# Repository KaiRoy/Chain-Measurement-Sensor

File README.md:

# Chain-Measurement-Sensor
The focus of this project was to create a Sensor that measures the wear of a chain for our Senior design course. The project partner for this project was the Hyster-Yale Group.

<!-- Insert Image Here -->

<!-- LINK SUMMARY VIDEO SOMEWHERE IN THE README!! -->

## Table of Contents

- [Description](#description)
- [Design](#design)
- [Current State](#current-state-of-the-project)
- [Post Project Notes](#post-project-notes)
- [Installation](#installation) <!-- Should I have Installation and Usage above or below the Design, Current State, Changes, etc? -->
- [Usage](#usage)
- [Credits](#credits)
- [License](#license)

## Description

The goal of this project is to create a chain elongation monitor for the Hyster-Yale Group that will automatically detect a worn lift chain and notify an operator to replace said chain. Chains, especially lifting chains, need to be frequently inspected to ensure they meet specifications. A 3% increase in a chain’s length can reduce its lifting capacity by 15%. This can become a dangerous hazard if out-of-spec chains are not caught. 

Currently, this inspection is either done by hand or by expensive third party devices, thus the creation of a cheap electronic alternative is very desirable. We plan to use three pairs of IR LEDs and IR receivers that will act as our sensors. These pairs will be situated in such a way that the IR “beam” will break when a chain link passes the sensor and reconnect in the gap between chain links. One pair will be used to measure the speed, while the other two will measure the “stretch” of the chain by recording the time difference between activations and calculating a length measurement.

In addition to the sensors, the device will consist of a power circuit to convert a Forklift’s 24V power into 5Vs, a CAN communication circuit, and a microcontroller to calculate the elongation based on the sensors and send those measurements via the CAN Circuit to the Hyster Vehicle. We chose an ATTiny814 for our microcontroller as it is a relatively small and cheap microcontroller and is capable of performing necessary functions, such as basic calculations and time measurement. 

Our project partner has specified that the device needs to meet four requirements:
 - The device needs to measure chain “stretch” (wear) within ±5% of the actual measurement.
 - The device, specifically the electronics, need to cost less than $15 or less at a production quantity of 15,000/yr
 - The device need to be robust enough to survive abrasive (high chain wear) applications
 - The device needs to communicate using the CAN communication protocol

At the end of our project, we were able to meet 3 of the 4 project partner requirements with the accuracy requirement being the one that was not met. This is mostly due to not having enough time to finish experimenting and debugging the code. With better time management and planning, we would have been able to finish the development of our code and could have met the final requirement.

## Designs

For the design portion of this project, the system's design was split into eight blocks with each person handling the design for two blocks. Adam handled the design of the Power Filter and the Power Regulator Blocks. Tianhao designed the Microcontroller and CAN Communication Circuits. The sensor and PCB blocks were handled by Kai. The code and the enclosure blocks were designed by Corbin. 

<!-- Power Blocks -->
The power converter block is based on an application schematic from the MC34063A-E datasheet to be used as a step-down converter. This block accomplishes the goal of reducing voltage and increasing current from 25V to 5V and current up to 500mA. The goal is to make the voltage and current levels safe for our microcontroller, CAN controller, and sensors to be used properly without overheating. The block contains the MC34063A/E chip itself, IN5819 Zener diode, three resistors (two are external to control the voltage output), three capacitors, and one inductor.

The power filter block is based on the LC filter schematic from [Digikey’s online LC filter calculator](https://www.digikey.com/en/resources/conversion-calculators/conversion-calculator-low-pass-and-high-pass-filter) to be used as a first order LC filter. This block accomplishes the goal of reducing frequency down to a fixed value of about less than 16kHz. This is to ensure that our high noise level of frequency is reduced so that our microcontroller and sensors can operate effectively. The block contains one inductor and one capacitor.

<!-- CAN Controller-->
The can block is built with one of the most practical stand-alone CAN controllers, MCP 2515 as the core. This module achieves the goal of communicating with Hyster Forklift’s electronics via 5 V digital serial signal. After achieving this goal, we can connect our device to the forklift with only two wires, so that the forklift can receive any information accurately. In this block, in addition to MCP 2515, we will also use TJA 1051 as the transceiver of the block to transmit or receive information transmitted through the CAN bus, an 8M Hz crystal oscillator as a bit rate regulator, an LED as an indicator, and some resistors and capacitors to stabilize the voltage and current of the part. In addition, we will also add two terminal block connectors to allow the output of the signal to adapt to more kinds of wires.

<!-- Micrcontroller -->
The Microcontroller block to be used in this project is the ATtiny 814. The module will be responsible for collecting and analyzing signals from the sensor, as well as controlling the operation of the signal transmitter. With the ATtiny 814, the project aims to achieve certain targets, such as measuring chain "stretch" within +/- 5% of the actual measurement, costing less than $10 at a production quantity of 15,000/yr, and outputting an analog (5V) or digital signal (CAN or other serial protocol signal).

<!-- Sensors -->
The Sensor block is implemented using three IR Breakbeam sensors. This document provides an overview of the overall block function including interface properties and a schematic, verification for the design in the form of a step-by-step testing process, and support for the validity of the design in the form of outside research and numerical justification addressing individual properties.

One sensor is placed in the ‘middle’ middle of the device and will be for measuring the speed of the Chain, while two sensors will be placed on the outer edges of the device and will be used for measuring/detecting the elongation of the chain.

The measurement of speed can be done by measuring the time difference between sensor activation as a chain link crosses the two central sensors and calculating the speed with that delta and the chain link length. For the elongation measurement/monitoring, the outer two sensors are placed with a specific distance between them, X amount of chain links. If positioned correctly, the two sensors will activate simultaneously with a chain that is not elongated and activates with some time delta with a chain that is elongated. This time delta coupled with the calculated speed can provide an estimate for the elongation measurement.

<!-- PCB -->
The Final PCB contains most of the circuits for all of the electronics blocks of the system. These circuits include the Power Filter, Power Converter, Microcontroller, and CAN Controller Blocks. This means that all of the outward-facing interfaces for these blocks, such as the sensor, power, and CAN connectors, are the interfaces for this block. 

<!-- Enclosure -->
The enclosure for this project will be a durable Pelican Case, created and distributed by the Pelican company. This ensures that our enclosure will be consistent, professionally made, and strong enough to protect our fragile components from the dangerous environment they will have to be in. Additionally, a piece of acrylic will be laser cut to allow for the mounting of the PCB and the guiding of wires through the walls of the enclosure, which will have holes cut into it.

## Current State of the Project

By the end of the project, we had a mostly working system. 

## Post Project Notes

## Installation

What EDA libraries and files are needed for this project?
- Various Component Libraries

<!--
## Usage

Provide instructions and examples for use. Include screenshots as needed.

To add a screenshot, create an `assets/images` folder in your repository and upload your screenshot to it. Then, using the relative filepath, add it to your README using the following syntax:

    ```md
    
    ```

## Features

If your project has a lot of features, list them here.

## Tests

-->

## Credits

List your collaborators, if any, with links to their GitHub profiles.
- Kai Roy
- 

If you used any third-party assets that require attribution, list the creators with links to their primary web presence in this section.
-

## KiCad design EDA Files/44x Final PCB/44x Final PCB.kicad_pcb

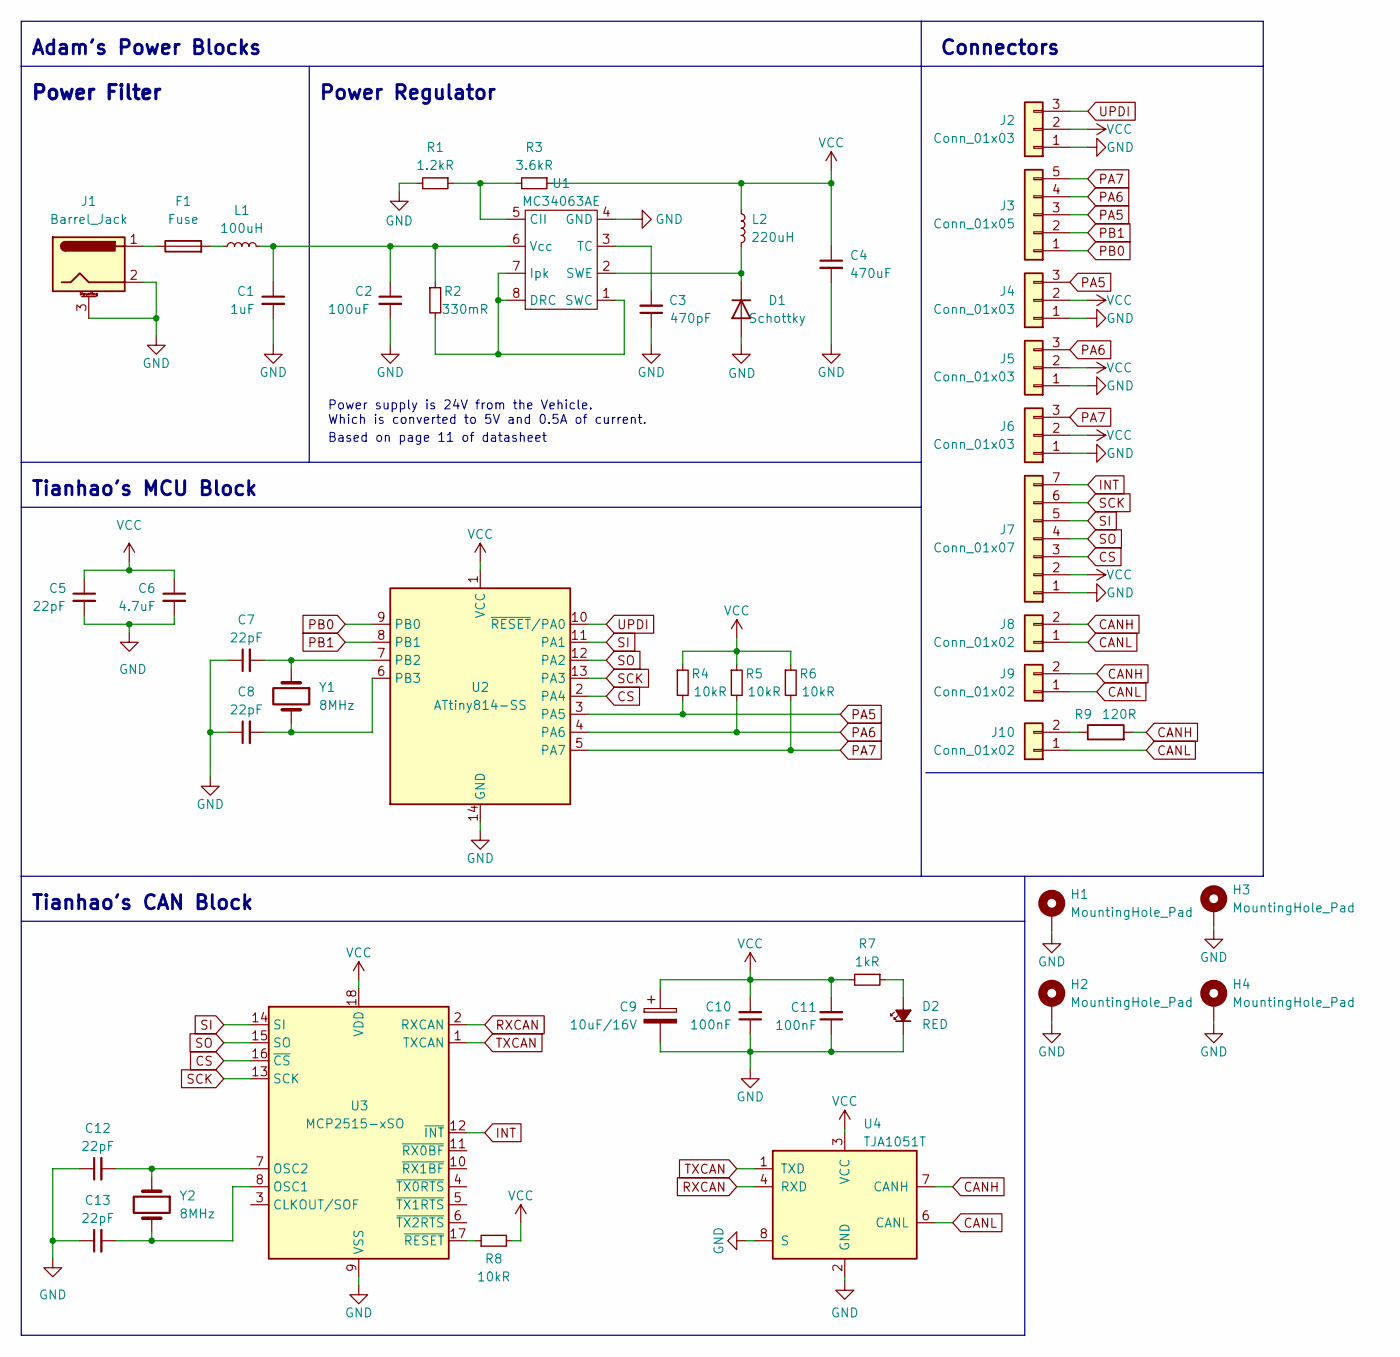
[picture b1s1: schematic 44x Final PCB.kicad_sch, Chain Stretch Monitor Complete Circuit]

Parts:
C1: 1uF; C_Radial_D5.0mm_H11.0mm_P2.00mm; Mouser 710-860020672005
C2: 100uF; C_Elec_10x10.2; Mouser 80-A781MN107M1HLAS30
C3: 470pF; C_0805_2012Metric_Pad1.18x1.45mm_HandSolder; Mouser 581-0805YC471K
C4: 470uF; CP_Elec_8x10; Mouser 581-APZ0809471M010R
C5, C7, C8, C12, C13: 22pF; C_0805_2012Metric_Pad1.18x1.45mm_HandSolder; Mouser 80-C0805C220J4HACTU
C6: 4.7uF; C_0805_2012Metric_Pad1.18x1.45mm_HandSolder; Mouser 81-GCJ21BR71C475KA1L
C9: 10uF/16V; C_1206_3216Metric_Pad1.33x1.80mm_HandSolder; Mouser 80-C1206C106Z4VACTU
C10, C11: 100nF; C_0805_2012Metric_Pad1.18x1.45mm_HandSolder; Mouser 581-0805YC104M4T2A
D1: Schottky; D_1206_3216Metric_Pad1.42x1.75mm_HandSolder; Mouser 581-SD1206T040S1R0
D2: RED; LED_0805_2012Metric_Pad1.15x1.40mm_HandSolder; Digikey LTST-C191KRKT
F1: Fuse; Fuseholder_Cylinder-5x20mm_Schurter_0031_8201_Horizontal_Op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; Mouser 693-0031.8201
H1, H2, H3, H4: MountingHole_Pad; MountingHole_3.2mm_M3_ISO14580_Pad_TopBottom
J1: Barrel_Jack; BarrelJack_CUI_PJ-102AH_Horizontal; Mouser 490-PJ-102AH
J2: Conn_01x03; PinHeader_1x03_P2.54mm_Vertical
J3: Conn_01x05; PinHeader_1x05_P2.54mm_Vertical
J4, J5, J6: Conn_01x03; JST_PH_B3B-PH-K_1x03_P2.00mm_Vertical
J7: Conn_01x07; PinHeader_1x07_P2.54mm_Vertical
J8: Conn_01x02; JST_PH_B2B-PH-K_1x02_P2.00mm_Vertical
J9, J10: Conn_01x02; PinHeader_1x02_P2.54mm_Vertical
L1: 100uH; L_Axial_L16.0mm_D6.3mm_P5.08mm_Vertical_Fastron_VHBCC; Mouser 530-SFAPI-101K-UL
L2: 220uH; L_Axial_L16.0mm_D7.5mm_P5.08mm_Vertical_Fastron_XHBCC; Mouser 542-5800-221-RC
R1: 1.2kR; R_0805_2012Metric_Pad1.20x1.40mm_HandSolder; Mouser 667-ERJ-PB6B1201V
R2: 330mR; R_1206_3216Metric_Pad1.30x1.75mm_HandSolder; Mouser 710-561070332096
R3: 3.6kR; R_0805_2012Metric_Pad1.20x1.40mm_HandSolder; Mouser 667-ERJ-PB6B3601V
R4, R5, R6, R8: 10kR; R_0805_2012Metric_Pad1.20x1.40mm_HandSolder; Mouser 667-ERJ-PB6B1002V
R7: 1kR; R_0805_2012Metric_Pad1.20x1.40mm_HandSolder; Mouser 667-ERJ-PB6B1001V
R9: 120R; R_0805_2012Metric_Pad1.20x1.40mm_HandSolder; Mouser 667-ERJ-T06J121V
U1: MC34063AE; SOIC-8_3.9x4.9mm_P1.27mm; Mouser 595-MC34063ADR
U2: ATtiny814-SS; SOIC-14_3.9x8.7mm_P1.27mm; Mouser 579-ATTINY814-SSN
U3: MCP2515-xSO; SOIC-18W_7.5x11.6mm_P1.27mm; Mouser 579-MCP2515-I/SO
U4: TJA1051T; SOIC-8_3.9x4.9mm_P1.27mm; Mouser 771-TJA1051T3118
Y1, Y2: 8MHz; Crystal_HC49-U_Vertical; Mouser 520-HCA800-18

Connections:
CANH: J8.2, J9.2, R9.2, U4.7 (CANH)
CANL: J8.1, J9.1, J10.1, U4.6 (CANL)
CS: J7.3, U2.2 (PA4), U3.16 (~CS)
GND: C1.2, C2.2, C3.1, C4.2, C5.2, C6.2, C7.1, C8.1, C9.2, C10.1, C11.1, C12.1, C13.1, D1.2 (A), D2.1 (K), H1.1, H2.1, H3.1, H4.1, J1.2, J1.3 (MountPin), J2.1, J4.1, J5.1, J6.1, J7.1, R1.2, U1.4 (GND), U2.14 (GND), U3.9 (VSS), U4.2 (GND), U4.8 (S)
INT: J7.7, U3.12 (~INT)
unnamed: C1.1, C2.1, L1.2, R2.1, U1.6 (Vcc)
unnamed: C3.2, U1.3 (TC)
unnamed: C7.2, U2.7 (PB2), Y1.1
unnamed: C8.2, U2.6 (PB3), Y1.2
unnamed: C12.2, U3.7 (OSC2), Y2.1
unnamed: C13.2, U3.8 (OSC1), Y2.2
unnamed: D1.1 (K), L2.2, U1.2 (SWE)
unnamed: D2.2 (A), R7.1
unnamed: F1.1, J1.1
unnamed: F1.2, L1.1
unnamed: J10.2, R9.1
unnamed: R1.1, R3.2, U1.5 (CII)
unnamed: R2.2, U1.1 (SWC), U1.7 (Ipk), U1.8 (DRC)
unnamed: R8.1, U3.17 (~RESET)
PA5: J3.3, J4.3, R4.2, U2.3 (PA5)
PA6: J3.4, J5.3, R5.2, U2.4 (PA6)
PA7: J3.5, J6.3, R6.2, U2.5 (PA7)
PB0: J3.1, U2.9 (PB0)
PB1: J3.2, U2.8 (PB1)
RXCAN: U3.2 (RXCAN), U4.4 (RXD)
SCK: J7.6, U2.13 (PA3), U3.13 (SCK)
SI: J7.5, U2.11 (PA1), U3.14 (SI)
SO: J7.4, U2.12 (PA2), U3.15 (SO)
TXCAN: U3.1 (TXCAN), U4.1 (TXD)
UPDI: J2.3, U2.10 (~RESET/PA0)
VCC: C4.1, C5.1, C6.1, C9.1, C10.2, C11.2, J2.2, J4.2, J5.2, J6.2, J7.2, L2.1, R3.1, R4.1, R5.1, R6.1, R7.2, R8.2, U2.1 (VCC), U3.18 (VDD), U4.3 (VCC)

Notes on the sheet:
Power Filter
Tianhao's MCU Block
Adam's Power Blocks
Tianhao's CAN Block
Power supply is 24V from the Vehicle. Which is converted to 5V and 0.5A of current.
Power Regulator
Connectors
Based on page 11 of datasheet

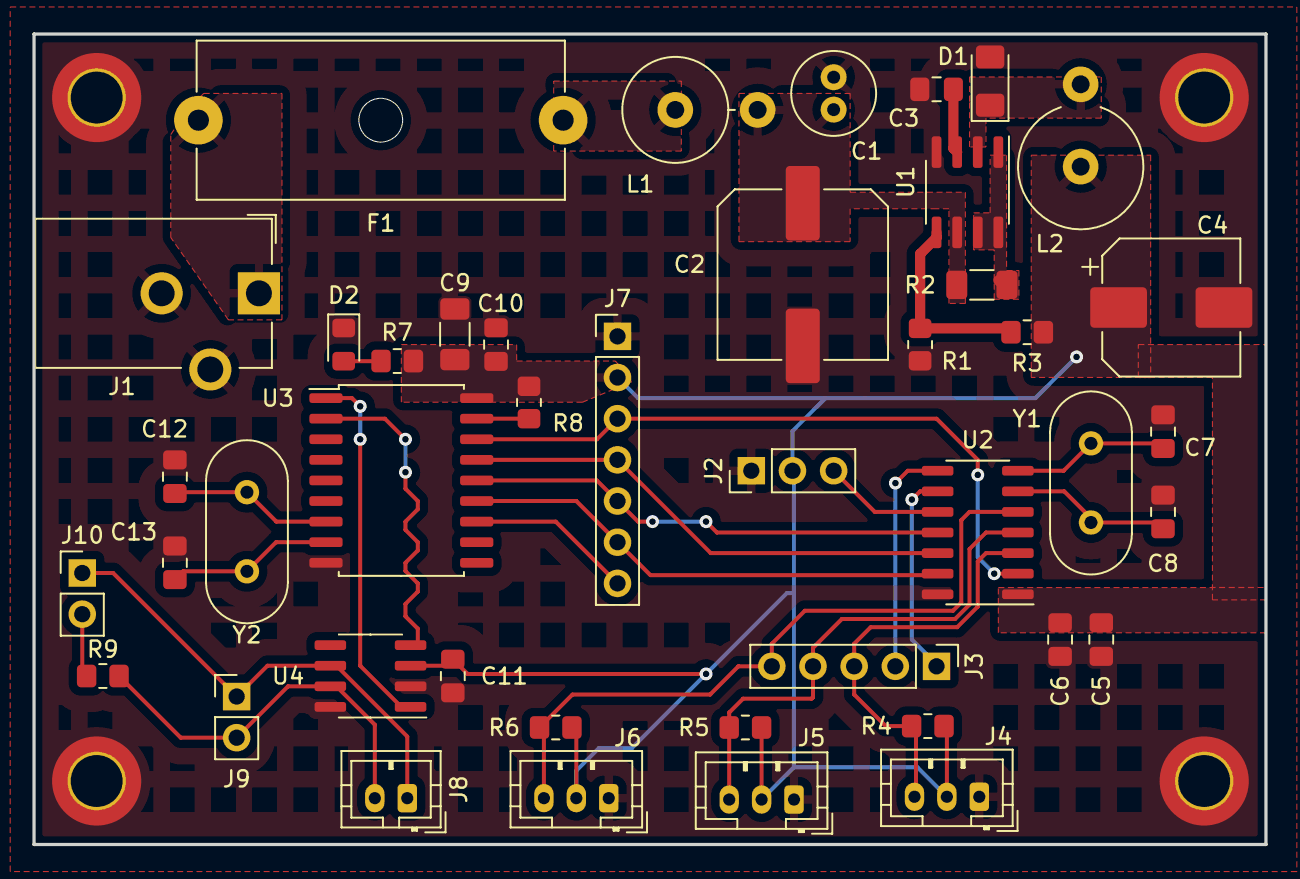
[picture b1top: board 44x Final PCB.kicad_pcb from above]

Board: 2 copper layers, 76.0 x 50.0 mm, 47 parts (0 on the bottom side), 31 nets.

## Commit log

2023-07-22 Transfer files to Repo
    Transferred a lot of necessary and useful files into the Repo including:
    Project Documentation
    Project Poster
    CAD files
    EDA Files
    Some Test Code
2023-07-24 Added Code Files
